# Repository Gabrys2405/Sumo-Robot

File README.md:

# Sumo-Robot
Sumo robot. Project in students scientific circle named Integra. The purpose of the project is to build and program a sumo robot.  Dimensions:  width = 10 +/- 0.5 cm length =  10 +/- 0.5 cm weight = 500 +/- 1g

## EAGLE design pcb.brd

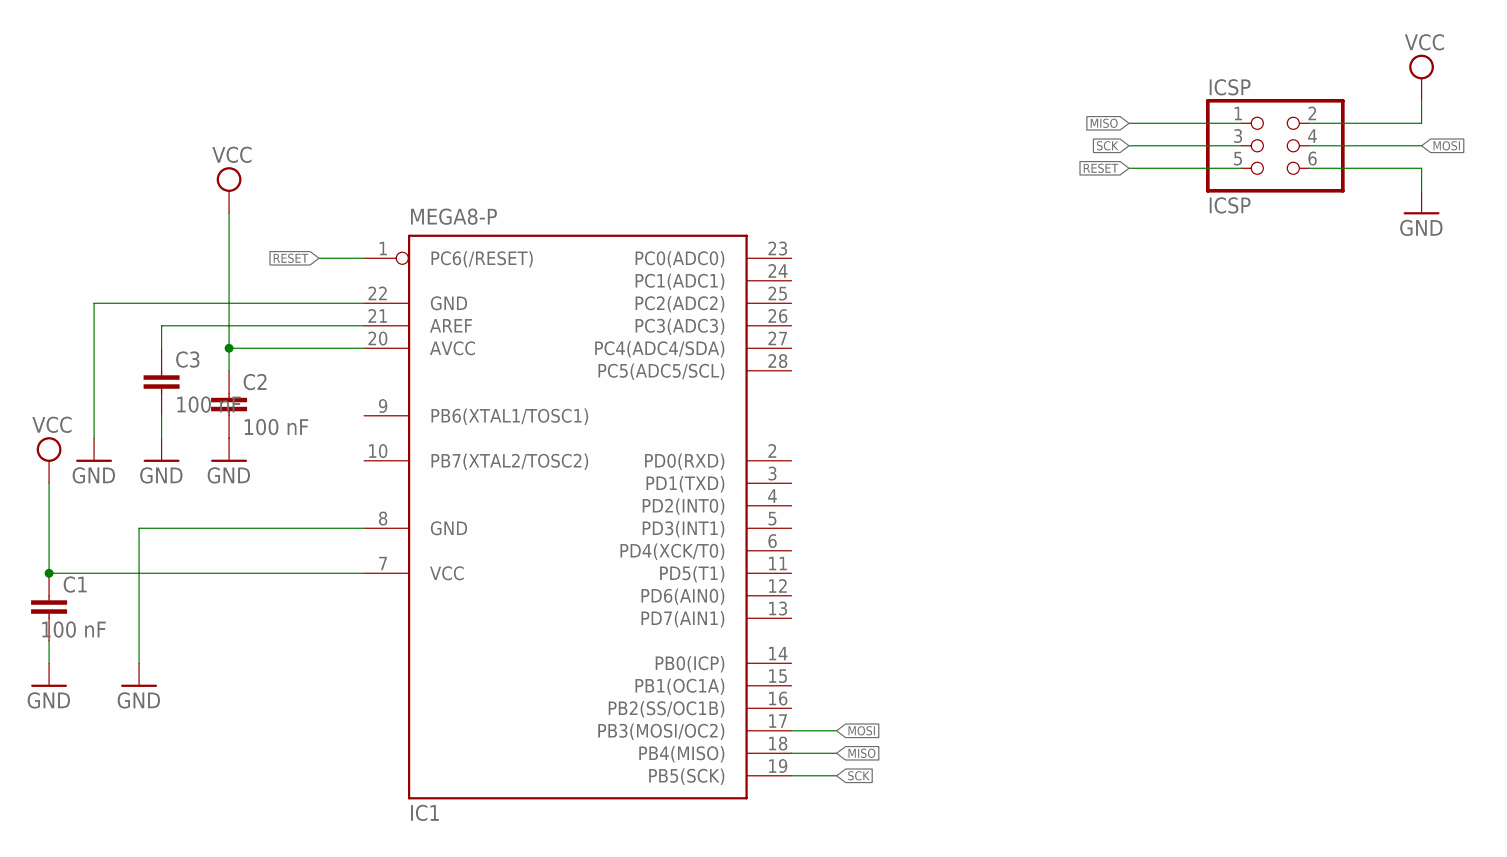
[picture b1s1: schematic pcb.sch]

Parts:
C1, C2, C3: 100 nF; C025-024X044
IC1: MEGA8-P; DIL28-3
ICSP: ICSP; 2X03

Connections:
GND: C1.2, C2.2, C3.2, IC1.8 (GND), IC1.22 (GND), ICSP.6
MISO: IC1.18 (PB4(MISO)), ICSP.1
MOSI: IC1.17 (PB3(MOSI/OC2)), ICSP.4
unnamed: C3.1, IC1.21 (AREF)
RESET: IC1.1 (PC6(/RESET)), ICSP.5
SCK: IC1.19 (PB5(SCK)), ICSP.3
VCC: C1.1, C2.1, IC1.7 (VCC), IC1.20 (AVCC), ICSP.2

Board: 2 copper layers, 5 parts (0 on the bottom side), 7 nets, no tracks yet.

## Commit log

2022-04-29 btanch
2022-04-30 components list
2022-05-01 first pcb draw
